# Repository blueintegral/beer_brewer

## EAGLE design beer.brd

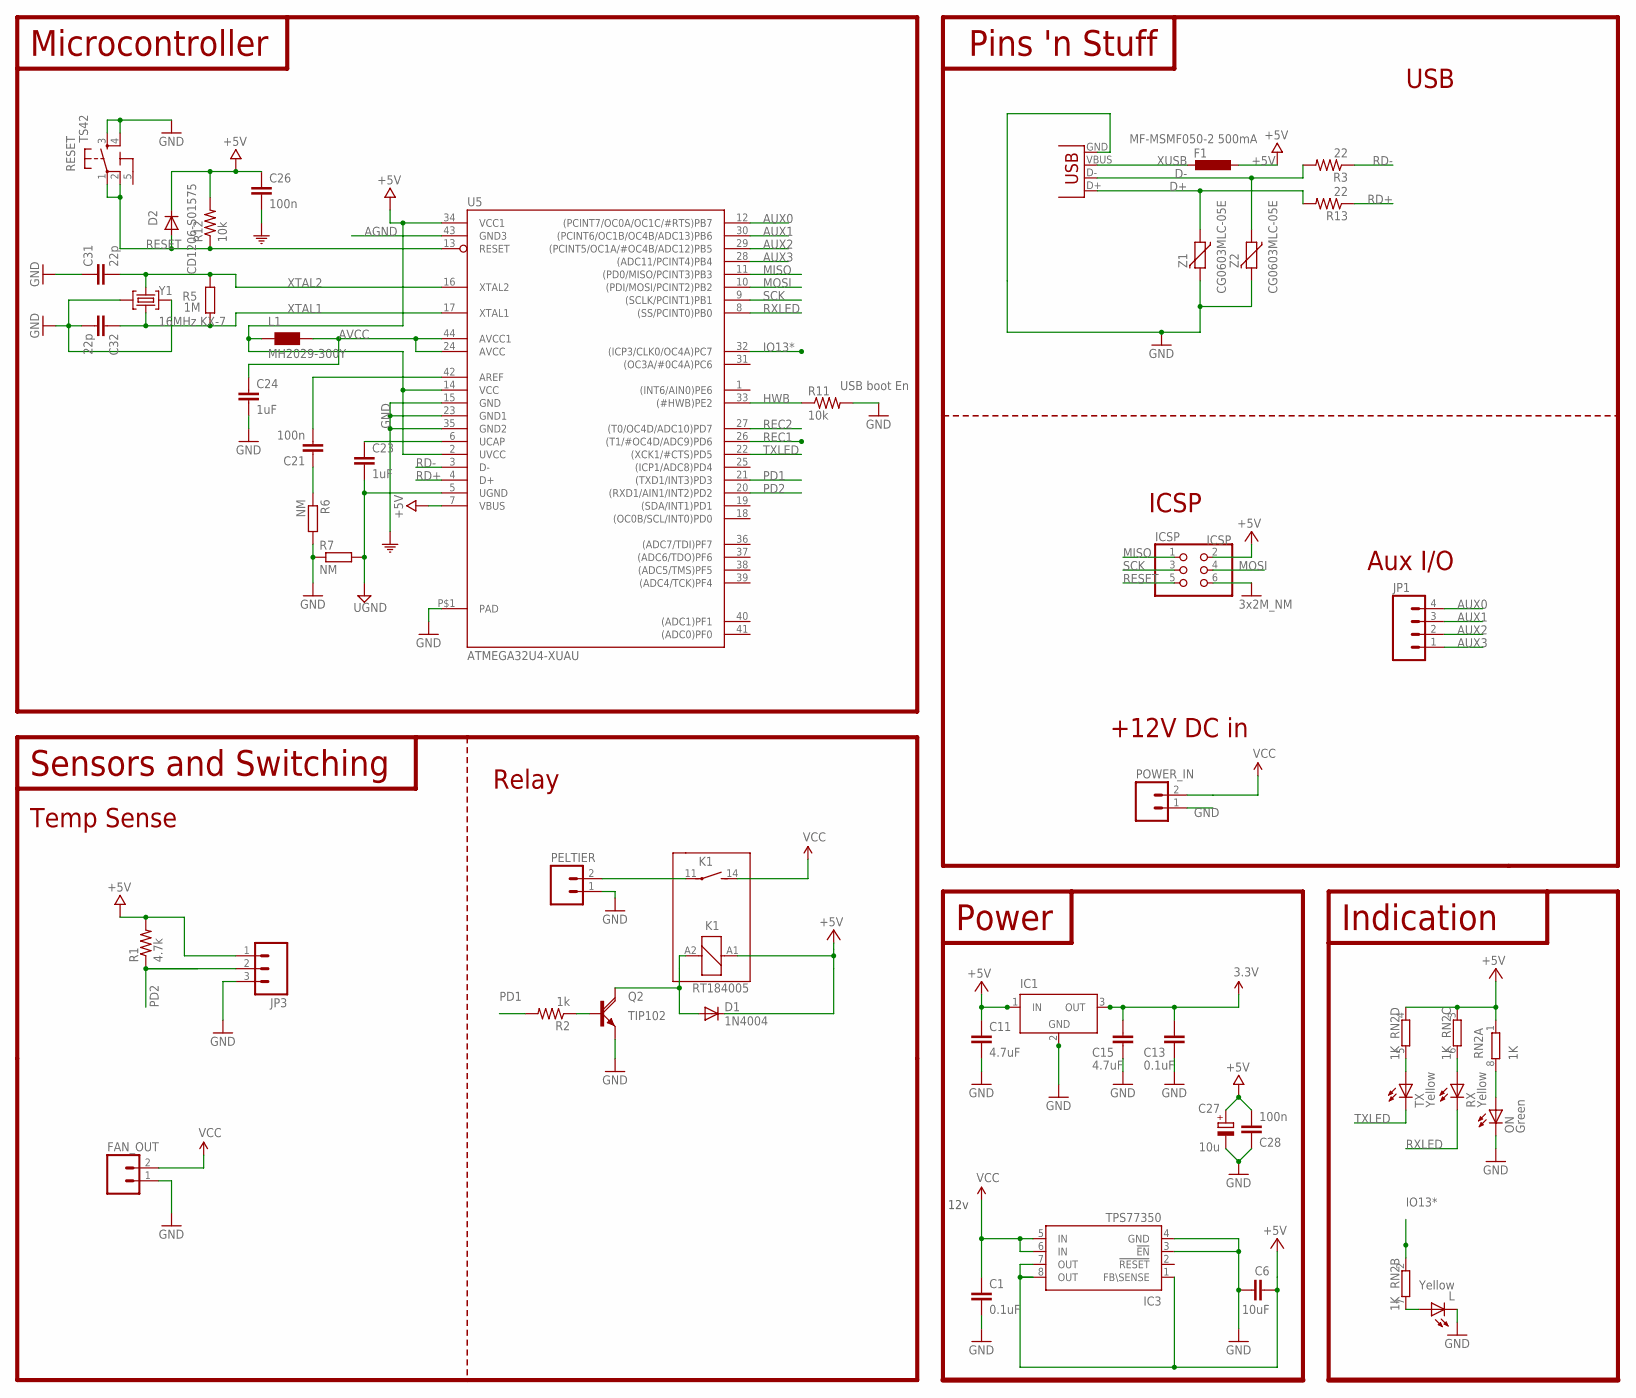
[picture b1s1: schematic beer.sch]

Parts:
C1, C13: 0.1uF; 0402-CAP
C6: 10uF; 0402-CAP
C11, C15: 4.7uF; 0402-CAP
C21, C26, C28: 100n; C0603-ROUND
C23, C24: 1uF; C0603-ROUND
C27: 10u; SMC_B
C31, C32: 22p; C0603-ROUND
D1: 1N4004; DO41-10
D2: CD1206-S01575; MINIMELF
F1: MF-MSMF050-2 500mA; L1812
FAN_OUT: M02PTH; 1X02
IC1: LT1129CST5; SOT223
IC3: TPS77350; SOP-08
ICSP: ICSP; 2X03
JP1: M04PTH; 1X04
JP3: M03PTH; 1X03
K1: RT184005; RT-N/O12A3.5
L: Yellow; CHIPLED_0805
L1: MH2029-300Y; 0805
ON: Green; CHIPLED_0805
PELTIER: M02PTH; 1X02
POWER_IN: M02PTH; 1X02
Q2: TIP120; TO220AH
R1: 4.7k; R0603
R2: 1k; R0603
R3, R13: 22; 0603-RES
R5: 1M; R0603-ROUND
R6, R7: NM; R0603-ROUND
R11, R12: 10k; R0603
RESET: TS42
RN2: 1K; CAY16
RX: Yellow; CHIPLED_0805
TX: Yellow; CHIPLED_0805
U5: ATMEGA32U4-XUAU; TQFP44-PAD
X2: USB-MICROB
Y1: 16MHz KX-7; CRYSTAL-3.2-2.5
Z1, Z2: CG0603MLC-05E; CT/CN0603

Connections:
3V3: C13.1, C15.1, IC1.3 (OUT)
5-GND: RESET.5 (5-GND)
+5V: C11.1, C26.1, C27.+, C28.2, D1.C, D2.C, F1.1, IC1.1 (IN), ICSP.2, JP3.1, K1.A1 (1), L1.1, R1.2, R12.2, RN2.1, RN2.3 (1), RN2.4 (1), U5.2 (UVCC), U5.7 (VBUS), U5.14 (VCC), U5.34 (VCC1)
AGND: C21.1, R6.1, U5.43 (GND3)
AREF: C21.2, U5.42 (AREF)
AUX0: JP1.4, U5.12 ((PCINT7/OC0A/OC1C/#RTS)PB7)
AUX1: JP1.3, U5.30 ((PCINT6/OC1B/OC4B/ADC13)PB6)
AUX2: JP1.2, U5.29 ((PCINT5/OC1A/#OC4B/ADC12)PB5)
AUX3: JP1.1, U5.28 ((ADC11/PCINT4)PB4)
AVCC: C24.1, L1.2, U5.24 (AVCC), U5.44 (AVCC1)
D+: R13.2, X2.D+, Z1.1
D-: R3.2, X2.D-, Z2.1
GND: C1.2, C6.1, C11.2, C13.2, C15.2, C24.2, C26.2, C27.-, C28.1, C31.1, C32.2, FAN_OUT.1, IC1.2 (GND), IC1.4 (GND), IC3.3 (!EN), IC3.4 (GND), ICSP.6, JP3.3, L.C, ON.C, PELTIER.1, POWER_IN.1, Q2.E, R6.2, R7.1, R11.2, RESET.3, RESET.4, U5.15 (GND), U5.23 (GND1), U5.35 (GND2), U5.P$1 (PAD), X2.GND, Y1.2 (GND), Y1.4 (GND), Z1.2, Z2.2
HWB: R11.1, U5.33 ((#HWB)PE2)
IO13*: RN2.2 (1), U5.32 ((ICP3/CLK0/OC4A)PC7)
MISO: ICSP.1, U5.11 ((PD0/MISO/PCINT3)PB3)
MOSI: ICSP.4, U5.10 ((PDI/MOSI/PCINT2)PB2)
unnamed: K1.11, PELTIER.2
unnamed: D1.A, K1.A2 (2), Q2.C
unnamed: RN2.5 (2), TX.A
unnamed: C6.2, IC3.1 (FB\SENSE), IC3.7 (OUT), IC3.8 (OUT)
unnamed: Q2.B, R2.1
unnamed: ON.A, RN2.8 (2)
unnamed: L.A, RN2.7 (2)
unnamed: RN2.6 (2), RX.A
PD1: R2.2, U5.21 ((TXD1/INT3)PD3)
PD2: JP3.2, R1.1, U5.20 ((RXD1/AIN1/INT2)PD2)
RD+: R13.1, U5.4 (D+)
RD-: R3.1, U5.3 (D-)
REC1: U5.26 ((T1/#OC4D/ADC9)PD6)
REC2: U5.27 ((T0/OC4D/ADC10)PD7)
RESET: D2.A, ICSP.5, R12.1, RESET.1, RESET.2, U5.13 (RESET)
RXLED: RX.C, U5.8 ((SS/PCINT0)PB0)
SCK: ICSP.3, U5.9 ((SCLK/PCINT1)PB1)
TXLED: TX.C, U5.22 ((XCK1/#CTS)PD5)
UCAP: C23.1, U5.6 (UCAP)
UGND: C23.2, R7.2, U5.5 (UGND)
VCC: C1.1, FAN_OUT.2, IC3.5 (IN), IC3.6 (IN), K1.14 (S), POWER_IN.2
XTAL1: C32.1, R5.1, U5.17 (XTAL1), Y1.1 (C1)
XTAL2: C31.2, R5.2, U5.16 (XTAL2), Y1.3 (C2)
XUSB: F1.2, X2.VBUS

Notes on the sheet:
Sensors and Switching
Power
Pins 'n Stuff
Microcontroller
USB boot En
Indication
Temp Sense
Relay
ICSP
USB
12v
+12V DC in
Aux I/O
TIP102

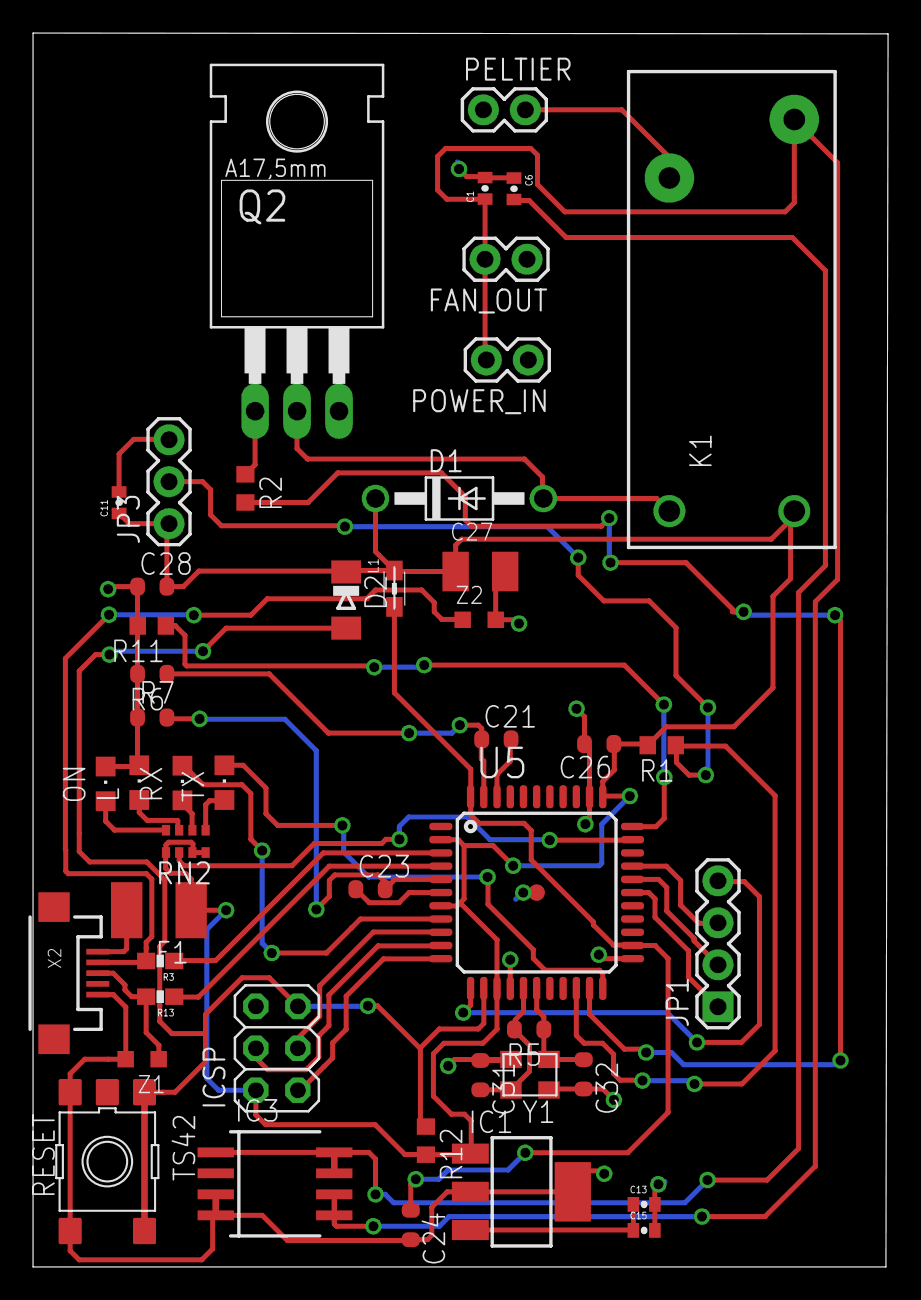
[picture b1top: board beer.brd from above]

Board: 2 copper layers, 51.7 x 74.7 mm, 47 parts (0 on the bottom side), 38 nets.

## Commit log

2013-06-17 Initial commit. Schematic done.
2013-07-12 Initial routing complete
2013-07-12 Added schematic export
